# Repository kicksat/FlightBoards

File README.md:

# mainboard
<p align="middle">
Main PCB driving the Kicksat-2 cubesat mothership. Its job is to depoly Sprites, which looks kind  of like this:
  </br>
</br>
Benchtop development hardware looks like this:

</p>

# License

[Creative Commons Attribution-ShareAlike 4.0 International](https://creativecommons.org/licenses/by-sa/4.0/)

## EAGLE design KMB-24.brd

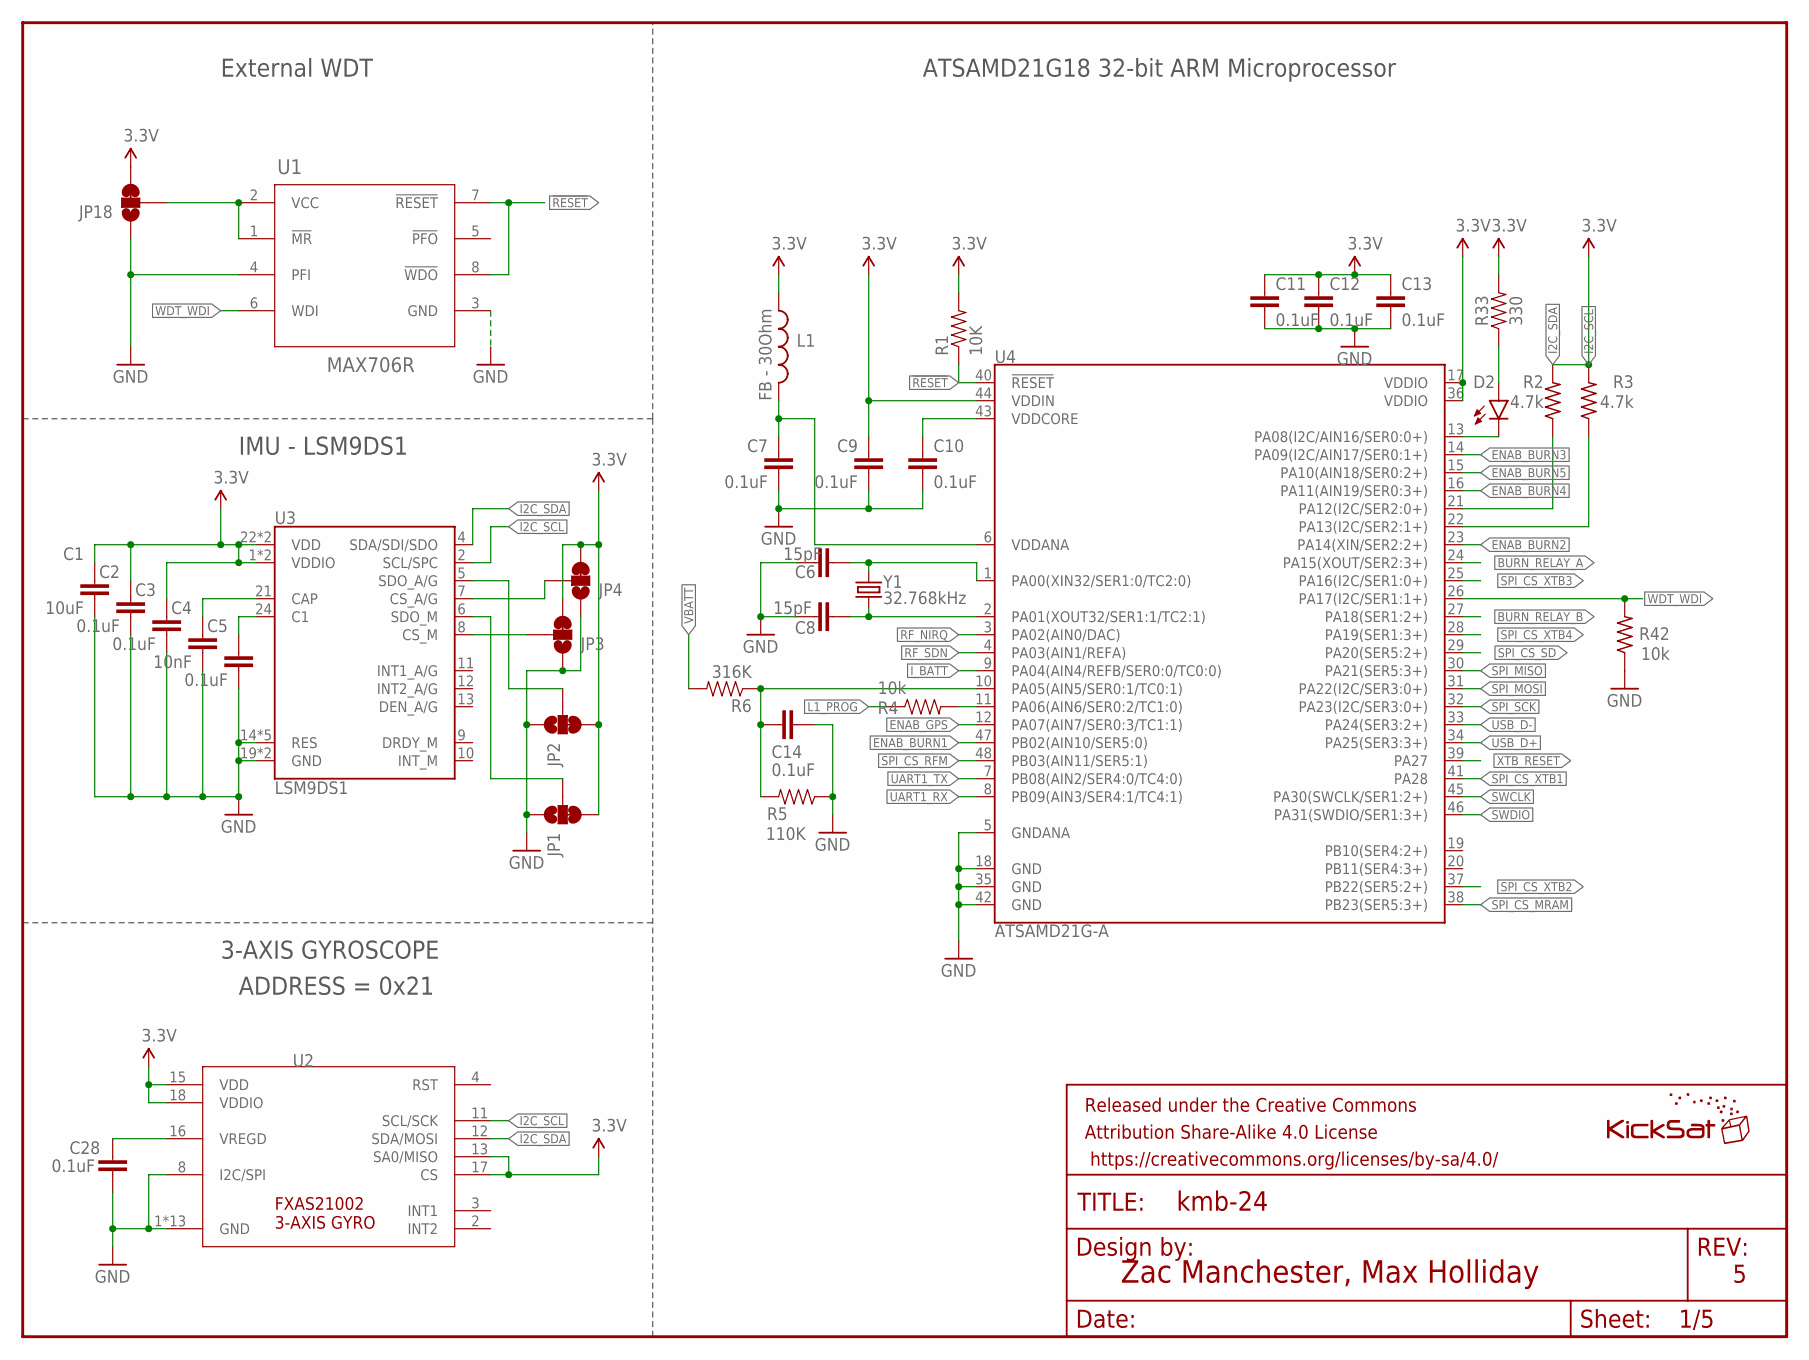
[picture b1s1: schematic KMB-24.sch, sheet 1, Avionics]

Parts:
C1: 10uF; 0603-CAP
C2, C3, C5, C7, C9, C10, C11, C12, C13, C14, C28: 0.1uF; 0603-CAP
C4: 10nF; 0603-CAP
C6, C8: 15pF; 0603-CAP@1
D2: GREEN; LED-0603
FRAME1: FRAME-LETTER; CREATIVE_COMMONS
JP1, JP2, JP3, JP4, JP18: JUMPER-PAD-3-2OF3_NC_BY_TRACE_SMALL; PAD-JUMPER-3-2OF3_NC_BY_TRACE_YES_SILK_FULL_BOX
L1: FB - 30Ohm; 0603
L2: KICKSAT_LOGO
R1: 10K; 0603-RES
R2, R3: 4.7k; R0603
R4: 10k; 0603-RES
R5: 110K; 0603-RES
R6: 316K; 0603-RES
R33: 330; 0603-RES
R42: 10k; R0603
U1: MAX706R; SO8
U2: FXAS21002FXAS21002; QFN50P456X400X100-24
U3: LSM9DS1; LGA24-8X4
U4: ATSAMD21G-A; TQFP-48
Y1: 32.768kHz; CRYSTAL-SMD-3.2X1.5MM

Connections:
3.3V: C1.1, C2.1, C3.1, C9.1, C11.1, C12.1, C13.1, JP1.3, JP2.3, JP3.3, JP4.3, JP18.3, L1.1, R1.2, R2.2, R3.2, R33.2, U2.13 (SA0/MISO), U2.15 (VDD), U2.17 (CS), U2.18 (VDDIO), U3.1 (VDDIO), U3.3 (VDDIO), U3.22 (VDD), U3.23 (VDD), U4.17 (VDDIO), U4.36 (VDDIO), U4.44 (VDDIN); also elsewhere on the board
!RESET: R1.1, U1.7 (!RESET), U1.8 (!WDO), U4.40 (!RESET!); also elsewhere on the board
BURN_RELAY_A: U4.24 (PA15(XOUT/SER2:3+)); also elsewhere on the board
BURN_RELAY_B: U4.27 (PA18(SER1:2+)); also elsewhere on the board
ENAB_BURN1: U4.47 (PB02(AIN10/SER5:0)); also elsewhere on the board
ENAB_BURN2: U4.23 (PA14(XIN/SER2:2+)); also elsewhere on the board
ENAB_BURN3: U4.14 (PA09(I2C/AIN17/SER0:1+)); also elsewhere on the board
ENAB_BURN4: U4.16 (PA11(AIN19/SER0:3+)); also elsewhere on the board
ENAB_BURN5: U4.15 (PA10(AIN18/SER0:2+)); also elsewhere on the board
ENAB_GPS: U4.12 (PA07(AIN7/SER0:3/TC1:1)); also elsewhere on the board
GND: C1.2, C2.2, C3.2, C4.2, C5.2, C6.1, C7.2, C8.2, C9.2, C10.2, C11.2, C12.2, C13.2, C14.2, C28.1, JP1.1, JP2.1, JP3.1, JP4.1, JP18.1, R5.1, R42.1, U1.3 (GND), U1.4 (PFI), U2.1 (GND), U2.5 (GND), U2.6 (GND), U2.7 (GND), U2.8 (I2C/SPI), U2.9 (GND), U2.10 (GND), U2.14 (GND), U2.19 (GND), U2.20 (GND), U2.21 (GND), U2.22 (GND), U2.23 (GND), U2.24 (GND), U3.14 (RES), U3.15 (RES), U3.16 (RES), U3.17 (RES), U3.18 (RES), U3.19 (GND), U3.20 (GND), U4.5 (GNDANA), U4.18 (GND), U4.35 (GND), U4.42 (GND); also elsewhere on the board
I2C_SCL: R3.1, U2.11 (SCL/SCK), U3.2 (SCL/SPC), U4.22 (PA13(I2C/SER2:1+))
I2C_SDA: R2.1, U2.12 (SDA/MOSI), U3.4 (SDA/SDI/SDO), U4.21 (PA12(I2C/SER2:0+))
I2C_SDOA/G: JP2.2, U3.5 (SDO_A/G)
I_BATT: U4.9 (PA04(AIN4/REFB/SER0:0/TC0:0)); also elsewhere on the board
L1_PROG: R4.1; also elsewhere on the board
unnamed: D2.A, R33.1
unnamed: C4.1, U3.21 (CAP)
unnamed: C5.1, U3.24 (C1)
unnamed: JP18.2, U1.1 (!MR), U1.2 (VCC)
unnamed: C14.1, R5.2, R6.1, U4.10 (PA05(AIN5/SER0:1/TC0:1))
unnamed: C7.1, L1.2, U4.6 (VDDANA)
unnamed: JP1.2, U3.6 (SDO_M)
unnamed: C28.2, U2.16 (VREGD)
unnamed: JP3.2, U3.8 (CS_M)
unnamed: JP4.2, U3.7 (CS_A/G)
unnamed: C6.2, U4.1 (PA00(XIN32/SER1:0/TC2:0)), Y1.P$2 (2)
unnamed: C8.1, U4.2 (PA01(XOUT32/SER1:1/TC2:1)), Y1.P$1 (1)
unnamed: R4.2, U4.11 (PA06(AIN6/SER0:2/TC1:0))
unnamed: D2.C, U4.13 (PA08(I2C/AIN16/SER0:0+))
RF_NIRQ: U4.3 (PA02(AIN0/DAC)); also elsewhere on the board
RF_SDN: U4.4 (PA03(AIN1/REFA)); also elsewhere on the board
SPI_CS_MRAM: U4.38 (PB23(SER5:3+)); also elsewhere on the board
SPI_CS_RFM: U4.48 (PB03(AIN11/SER5:1)); also elsewhere on the board
SPI_CS_SD: U4.29 (PA20(SER5:2+)); also elsewhere on the board
SPI_CS_XTB1: U4.41 (PA28); also elsewhere on the board
SPI_CS_XTB2: U4.37 (PB22(SER5:2+)); also elsewhere on the board
SPI_CS_XTB3: U4.25 (PA16(I2C/SER1:0+)); also elsewhere on the board
SPI_CS_XTB4: U4.28 (PA19(SER1:3+)); also elsewhere on the board
SPI_MISO: U4.30 (PA21(SER5:3+)); also elsewhere on the board
SPI_MOSI: U4.31 (PA22(I2C/SER3:0+)); also elsewhere on the board
SPI_SCK: U4.32 (PA23(I2C/SER3:0+)); also elsewhere on the board
SWCLK: U4.45 (PA30(SWCLK/SER1:2+)); also elsewhere on the board
SWDIO: U4.46 (PA31(SWDIO/SER1:3+)); also elsewhere on the board
UART1_RX: U4.8 (PB09(AIN3/SER4:1/TC4:1)); also elsewhere on the board
UART1_TX: U4.7 (PB08(AIN2/SER4:0/TC4:0)); also elsewhere on the board
USB_D+: U4.34 (PA25(SER3:3+)); also elsewhere on the board
USB_D-: U4.33 (PA24(SER3:2+)); also elsewhere on the board
VBATT: R6.2; also elsewhere on the board
VDDCORE3: C10.1, U4.43 (VDDCORE)
WDT_WDI: R42.2, U1.6 (WDI), U4.26 (PA17(I2C/SER1:1+))
XTB_RESET: U4.39 (PA27); also elsewhere on the board

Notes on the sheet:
Zac Manchester, Max Holliday
ATSAMD21G18 32-bit ARM Microprocessor
IMU - LSM9DS1
External WDT
3-AXIS GYROSCOPE
ADDRESS = 0x21

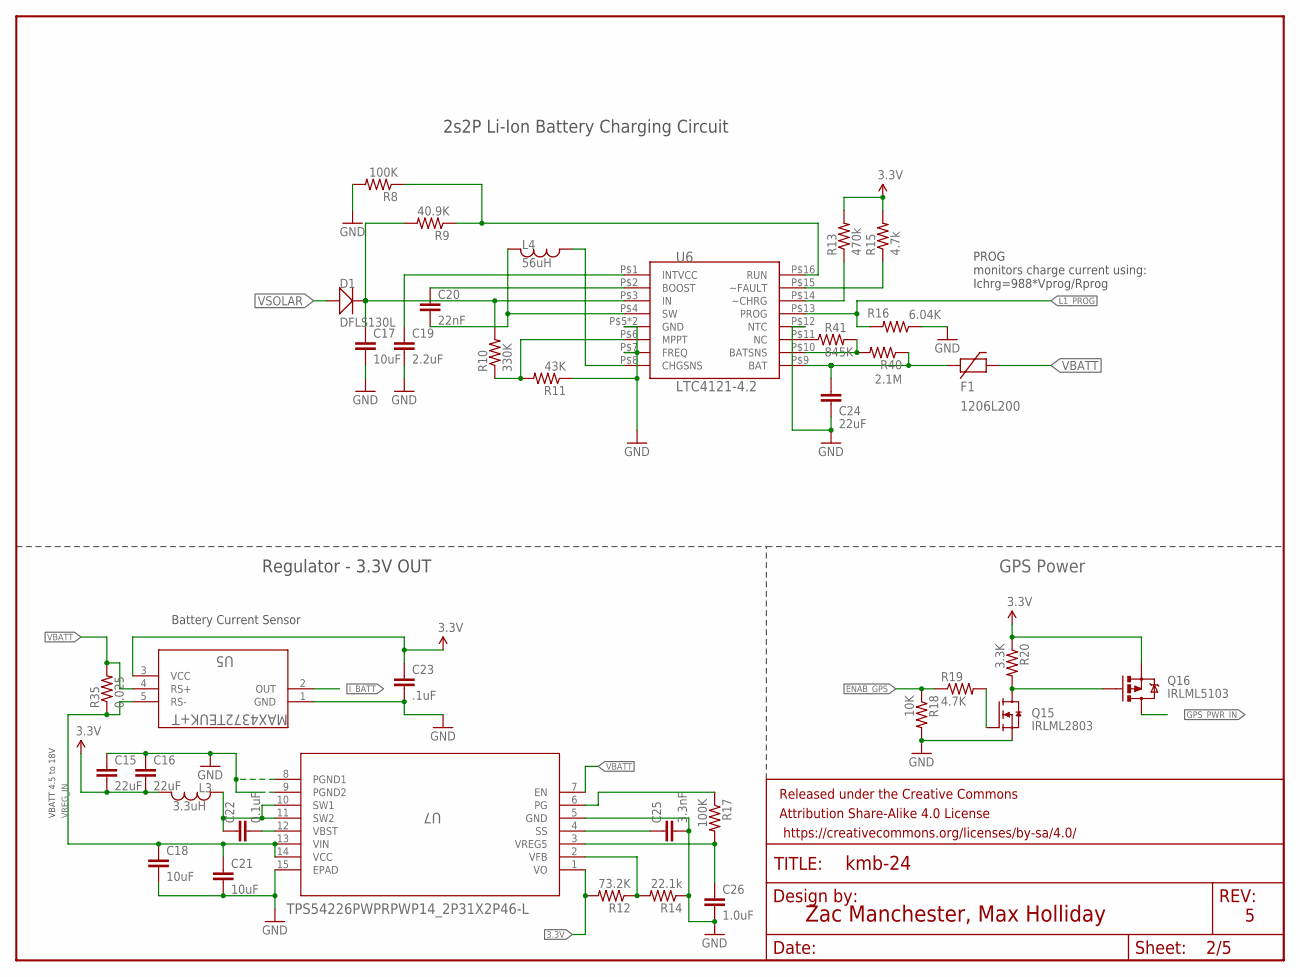
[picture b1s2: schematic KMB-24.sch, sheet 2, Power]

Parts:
C15, C16: 22uF; 0805
C17, C18, C21: 10uF; 0603
C19: 2.2uF; 0603
C20: 22nF; 0603
C22: 0.1uF; 0603
C23: .1uF; 0603-CAP@1
C24: 22uF; 0603
C25: 3.3nF; 0603
C26: 1.0uF; 0603
D1: DFLS130L; PWRDI-123
F1: 1206L200; 1206
FRAME2: FRAME-LETTER; CREATIVE_COMMONS
L3: 3.3uH; 1812
L4: 56uH; 1812
Q15: IRLML2803; SOT-23
Q16: IRLML5103; SOT23-3
R8, R17: 100K; R0603
R9: 40.9K; R0603
R10: 330K; R0603
R11: 43K; R0603
R12: 73.2K; R0603
R13: 470k; R0603
R14: 22.1k; R0603
R15: 4.7k; R0603
R16: 6.04K; R0603
R18: 10K; R0603
R19: 4.7K; R0603
R20: 3.3K; R0603
R35: 0.025; R2512
R40: 2.1M; R0603
R41: 845K; R0603
U5: MAX4372TEUK+T; 21-0057F
U6: LTC4121-4.2; QFN-16-PAD
U7: TPS54226PWPRPWP14_2P31X2P46-L; PWP14_2P31X2P46-L

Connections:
3.3V: C15.2, C16.2, C23.1, L3.P$1, Q16.2 (S), R12.2, R13.2, R15.2, R20.1, U5.3 (VCC), U7.1 (VO); also elsewhere on the board
ENAB_GPS: R18.1, R19.1; also elsewhere on the board
GND: C15.1, C16.1, C17.2, C18.2, C19.2, C21.2, C23.2, C24.2, C25.2, C26.2, Q15.2 (S), R8.2, R11.1, R14.1, R16.1, R18.2, U5.1 (GND), U6.P$5 (GND), U6.P$7 (FREQ), U6.P$12 (NTC), U6.P$17 (GND), U7.5 (GND), U7.8 (PGND1), U7.9 (PGND2), U7.15 (EPAD); also elsewhere on the board
GPS_PWR_IN: Q16.3 (D); also elsewhere on the board
I_BATT: U5.2 (OUT); also elsewhere on the board
L1_CHG: R8.1, R9.1, U6.P$16 (RUN)
L1_FAULTN: R15.1, U6.P$15 (~FAULT)
L1_PROG: R16.2, U6.P$13 (PROG); also elsewhere on the board
LION1: C24.1, F1.1, R40.1, U6.P$9 (BAT)
unnamed: C22.1, L3.P$2, U7.10 (SW1), U7.11 (SW2)
unnamed: Q15.1 (G), R19.2
unnamed: Q15.3 (D), Q16.1 (G), R20.2
unnamed: C22.2, U7.12 (VBST)
unnamed: R40.2, R41.2, U6.P$10 (BATSNS)
unnamed: C20.2, L4.P$1, U6.P$4 (SW)
unnamed: C20.1, U6.P$2 (BOOST)
unnamed: C19.1, U6.P$1 (INTVCC)
unnamed: R10.1, R11.2, U6.P$6 (MPPT)
unnamed: L4.P$2, U6.P$8 (CHGSNS)
unnamed: R13.1, U6.P$14 (~CHRG)
unnamed: C26.1, R17.2, U7.3 (VREG5)
unnamed: C25.1, U7.4 (SS)
unnamed: R12.1, R14.2, U7.2 (VFB)
unnamed: R41.1, U6.P$11 (NC)
PGOOD: R17.1, U7.6 (PG)
VBATT: F1.2, R35.2, U5.4 (RS+), U7.7 (EN); also elsewhere on the board
VREG_IN: C18.1, C21.1, R35.1, U5.5 (RS-), U7.13 (VIN), U7.14 (VCC)
VSOLAR: D1.A; also elsewhere on the board
VSOLAR_IN: C17.1, D1.C, R9.2, R10.2, U6.P$3 (IN)

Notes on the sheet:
Battery Current Sensor
Zac Manchester, Max Holliday
GPS Power
2s2P Li-Ion Battery Charging Circuit
Regulator - 3.3V OUT
VBATT 4.5 to 18V
PROG monitors charge current using: Ichrg=988*Vprog/Rprog

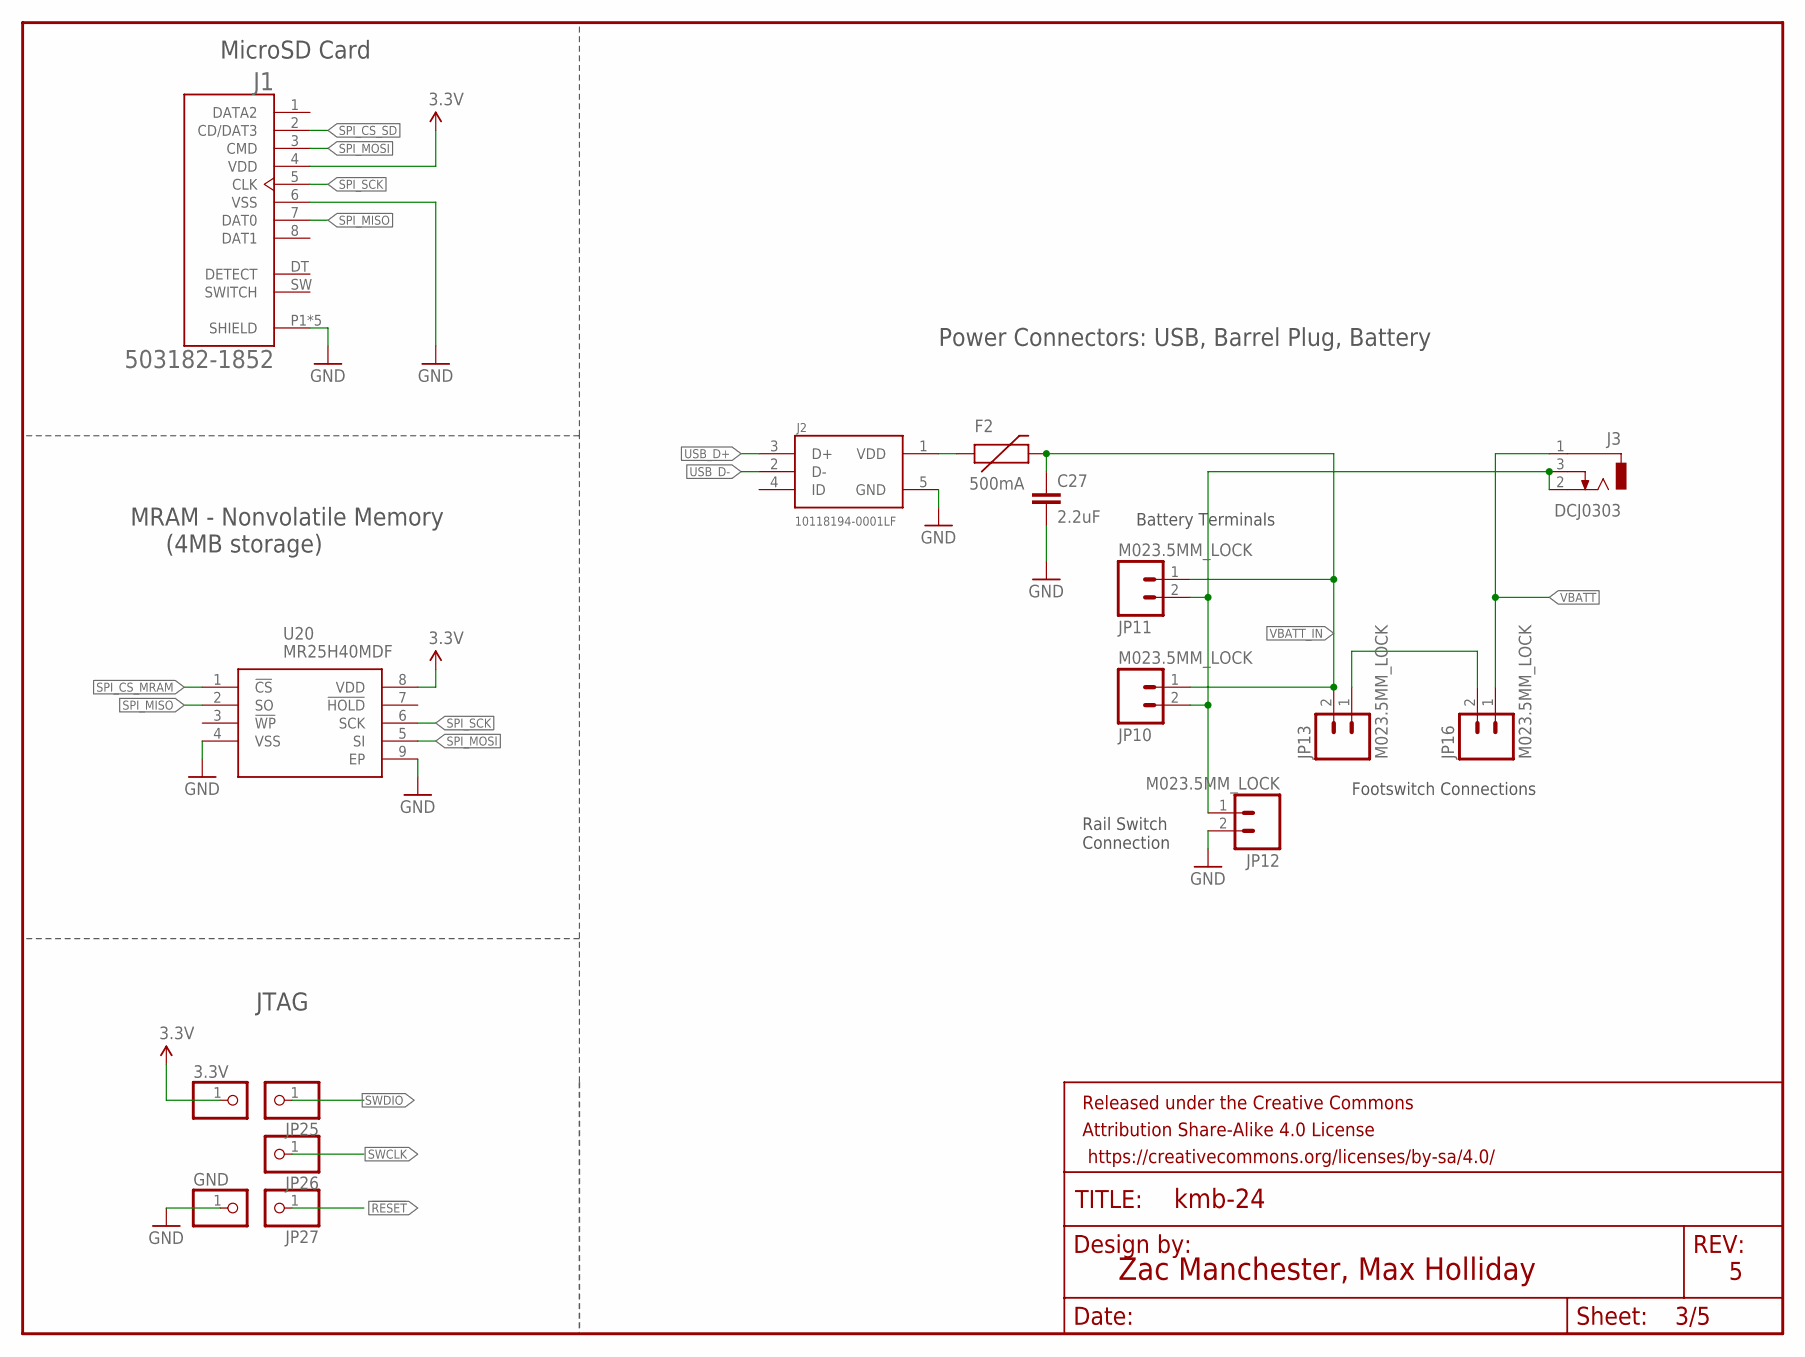
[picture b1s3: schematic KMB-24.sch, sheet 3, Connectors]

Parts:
3.3V: PINHD-1X1; 1X01
C27: 2.2uF; 0603
F2: 500mA; PTC-1206
FRAME3: FRAME-LETTER; CREATIVE_COMMONS
GND: PINHD-1X1; 1X01
J1: 503182-1852; MOLEX_503182-1852
J2: 10118194-0001LF; FRAMATOME_10118194-0001LF
J3: DCJ0303
JP10, JP11, JP12, JP13, JP16: M023.5MM_LOCK; SCREWTERMINAL-3.5MM-2_LOCK
JP25, JP26, JP27: PINHD-1X1; 1X01
U20: MR25H40MDF; SON127P600X500X90-9N

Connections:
3.3V: 3.3V.1, J1.4 (VDD), U20.8 (VDD); also elsewhere on the board
!RESET: JP27.1; also elsewhere on the board
GND: C27.2, GND.1, J1.6 (VSS), J1.P1 (SHIELD), J1.P2 (SHIELD), J1.P3 (SHIELD), J1.P4 (SHIELD), J1.P5 (SHIELD), J2.5 (GND), JP12.2, U20.4 (VSS), U20.9 (EP); also elsewhere on the board
unnamed: JP13.1, JP16.2
unnamed: F2.1, J2.1 (VDD)
unnamed: J3.2, J3.3, JP10.2, JP11.2, JP12.1
SPI_CS_MRAM: U20.1 (!CS); also elsewhere on the board
SPI_CS_SD: J1.2 (CD/DAT3); also elsewhere on the board
SPI_MISO: J1.7 (DAT0), U20.2 (SO); also elsewhere on the board
SPI_MOSI: J1.3 (CMD), U20.5 (SI); also elsewhere on the board
SPI_SCK: J1.5 (CLK), U20.6 (SCK); also elsewhere on the board
SWCLK: JP26.1; also elsewhere on the board
SWDIO: JP25.1; also elsewhere on the board
USB_D+: J2.3 (D+); also elsewhere on the board
USB_D-: J2.2 (D-); also elsewhere on the board
VBATT: J3.1, JP16.1; also elsewhere on the board
VBATT_IN: C27.1, F2.2, JP10.1, JP11.1, JP13.2

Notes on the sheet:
Footswitch Connections
Battery Terminals
Rail Switch Connection
Zac Manchester, Max Holliday
JTAG
Power Connectors: USB, Barrel Plug, Battery
MicroSD Card
MRAM - Nonvolatile Memory (4MB storage)

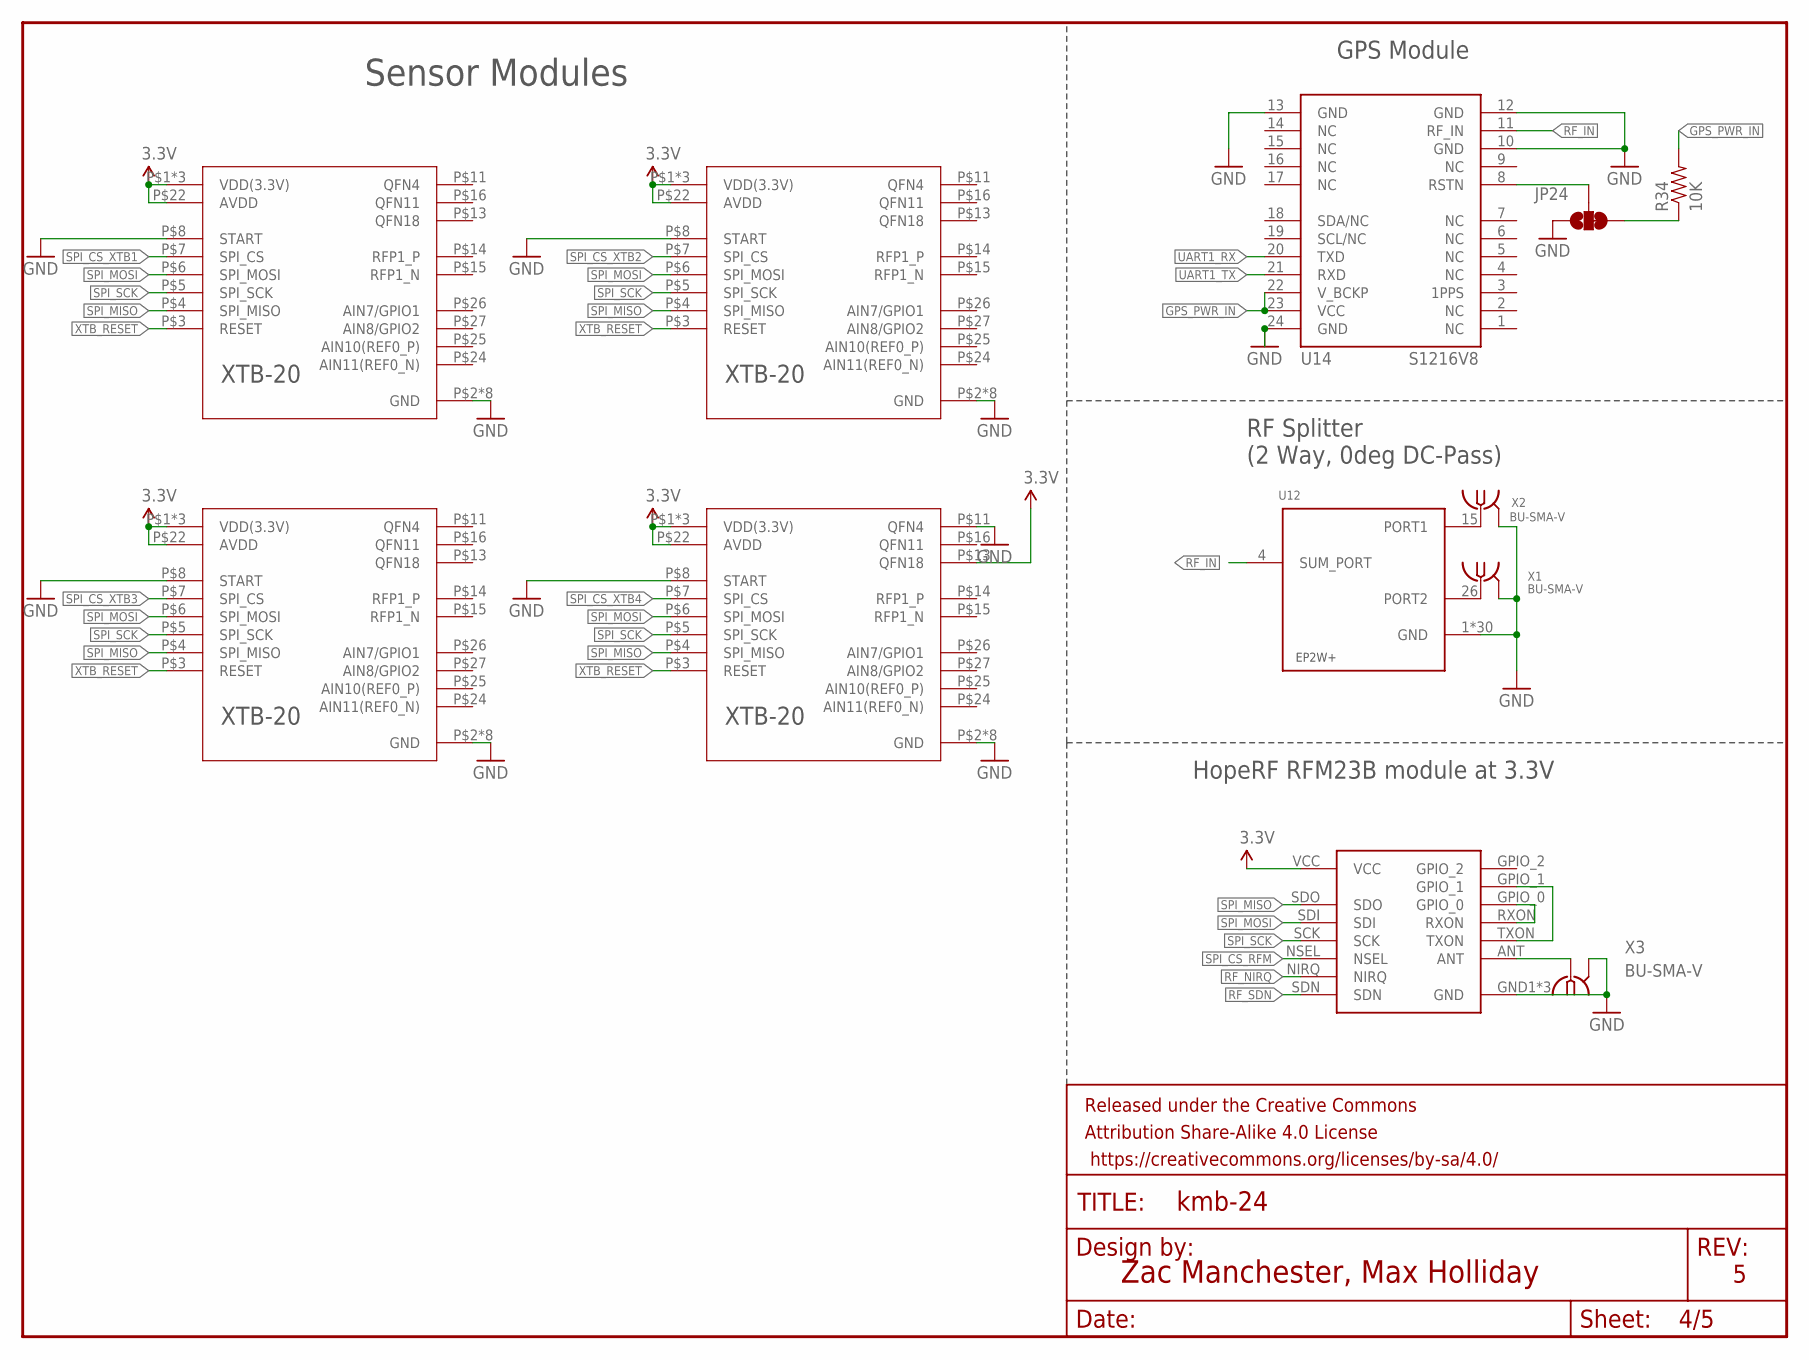
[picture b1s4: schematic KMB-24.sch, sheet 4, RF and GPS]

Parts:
FRAME4: FRAME-LETTER; CREATIVE_COMMONS
JP24: JUMPER-PAD-3-2OF3_NC_BY_TRACE_SMALL; PAD-JUMPER-3-2OF3_NC_BY_TRACE_YES_SILK_FULL_BOX
R34: 10K; 0603-RES
U12: EP2W+; QFN32-5X5MM
U13: RFM23BP
U14: S1216V8; S1216_24PIN_PACKAGE
U15, U16, U17, U18: XTB_2018_07_15; XTB28_MEZ
X1, X2, X3: BU-SMA-V

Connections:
3.3V: U13.VCC, U15.P$1 (VDD(3.3V)), U15.P$20 (VDD(3.3V)), U15.P$22 (AVDD), U15.P$28 (VDD(3.3V)), U16.P$1 (VDD(3.3V)), U16.P$20 (VDD(3.3V)), U16.P$22 (AVDD), U16.P$28 (VDD(3.3V)), U17.P$1 (VDD(3.3V)), U17.P$20 (VDD(3.3V)), U17.P$22 (AVDD), U17.P$28 (VDD(3.3V)), U18.P$1 (VDD(3.3V)), U18.P$13 (QFN18), U18.P$20 (VDD(3.3V)), U18.P$22 (AVDD), U18.P$28 (VDD(3.3V)); also elsewhere on the board
GND: JP24.1, U12.1 (GND), U12.2 (GND), U12.3 (GND), U12.5 (GND), U12.6 (GND), U12.7 (GND), U12.8 (GND), U12.9 (GND), U12.10 (GND), U12.11 (GND), U12.12 (GND), U12.13 (GND), U12.14 (GND), U12.16 (GND), U12.17 (GND), U12.18 (GND), U12.19 (GND), U12.20 (GND), U12.21 (GND), U12.22 (GND), U12.23 (GND), U12.24 (GND), U12.25 (GND), U12.27 (GND), U12.28 (GND), U12.29 (GND), U12.30 (GND), U12.31 (GND), U12.32 (GND), U12.EP (GND), U13.GND1 (GND), U13.GND2 (GND), U13.GND3 (GND), U14.10 (GND), U14.12 (GND), U14.13 (GND), U14.24 (GND), U15.P$2 (GND), U15.P$8 (START), U15.P$9 (GND), U15.P$10 (GND), U15.P$12 (GND), U15.P$17 (GND), U15.P$19 (GND), U15.P$21 (GND), U15.P$23 (GND), U16.P$2 (GND), U16.P$8 (START), U16.P$9 (GND), U16.P$10 (GND), U16.P$12 (GND), U16.P$17 (GND), U16.P$19 (GND), U16.P$21 (GND), U16.P$23 (GND), U17.P$2 (GND), U17.P$8 (START), U17.P$9 (GND), U17.P$10 (GND), U17.P$12 (GND), U17.P$17 (GND), U17.P$19 (GND), U17.P$21 (GND), U17.P$23 (GND), U18.P$2 (GND), U18.P$8 (START), U18.P$9 (GND), U18.P$10 (GND), U18.P$11 (QFN4), U18.P$12 (GND), U18.P$17 (GND), U18.P$19 (GND), U18.P$21 (GND), U18.P$23 (GND), X1.2, X1.3 (2), X1.4 (2), X1.5 (2), X2.2, X2.3 (2), X2.4 (2), X2.5 (2), X3.2, X3.3 (2), X3.4 (2), X3.5 (2); also elsewhere on the board
GPS_PWR_IN: R34.2, U14.22 (V_BCKP), U14.23 (VCC); also elsewhere on the board
unnamed: JP24.2, U14.8 (RSTN)
unnamed: U12.15 (PORT1), X2.1
unnamed: U12.26 (PORT2), X1.1
unnamed: U13.ANT, X3.1
unnamed: JP24.3, R34.1
unnamed: U13.GPIO_0, U13.RXON
unnamed: U13.GPIO_1, U13.TXON
RF_IN: U12.4 (SUM_PORT), U14.11 (RF_IN)
RF_NIRQ: U13.NIRQ; also elsewhere on the board
RF_SDN: U13.SDN; also elsewhere on the board
SPI_CS_RFM: U13.NSEL; also elsewhere on the board
SPI_CS_XTB1: U15.P$7 (SPI_CS); also elsewhere on the board
SPI_CS_XTB2: U16.P$7 (SPI_CS); also elsewhere on the board
SPI_CS_XTB3: U17.P$7 (SPI_CS); also elsewhere on the board
SPI_CS_XTB4: U18.P$7 (SPI_CS); also elsewhere on the board
SPI_MISO: U13.SDO, U15.P$4 (SPI_MISO), U16.P$4 (SPI_MISO), U17.P$4 (SPI_MISO), U18.P$4 (SPI_MISO); also elsewhere on the board
SPI_MOSI: U13.SDI, U15.P$6 (SPI_MOSI), U16.P$6 (SPI_MOSI), U17.P$6 (SPI_MOSI), U18.P$6 (SPI_MOSI); also elsewhere on the board
SPI_SCK: U13.SCK, U15.P$5 (SPI_SCK), U16.P$5 (SPI_SCK), U17.P$5 (SPI_SCK), U18.P$5 (SPI_SCK); also elsewhere on the board
UART1_RX: U14.20 (TXD); also elsewhere on the board
UART1_TX: U14.21 (RXD); also elsewhere on the board
XTB_RESET: U15.P$3 (RESET), U16.P$3 (RESET), U17.P$3 (RESET), U18.P$3 (RESET); also elsewhere on the board

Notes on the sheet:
GPS Module
Zac Manchester, Max Holliday
HopeRF RFM23B module at 3.3V
RF Splitter (2 Way, 0deg DC-Pass)
Sensor Modules

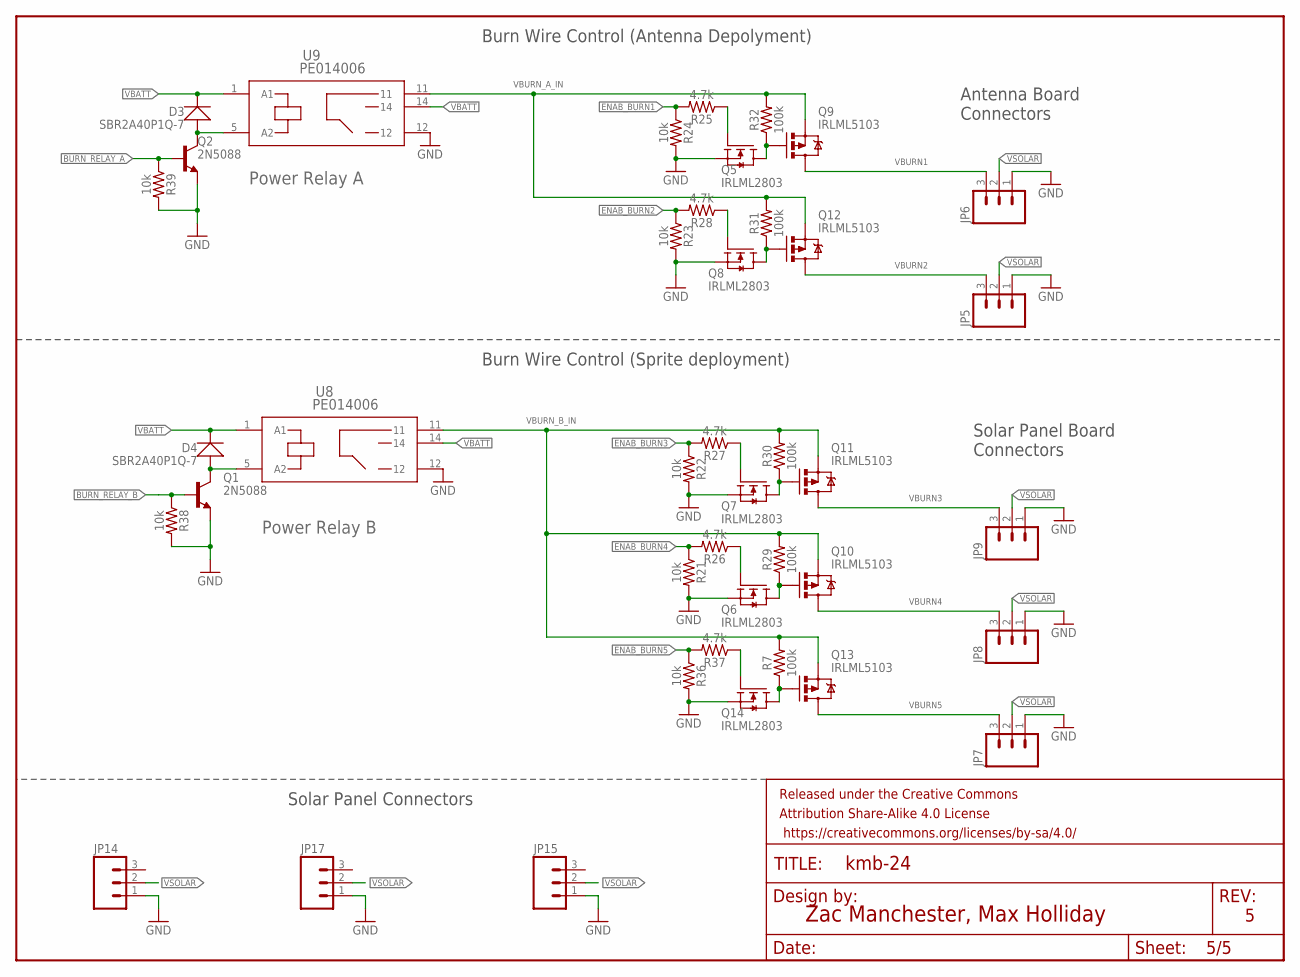
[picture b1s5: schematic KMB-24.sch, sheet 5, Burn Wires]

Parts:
D3, D4: SBR2A40P1Q-7; PWRDI-123
FRAME5: FRAME-LETTER; CREATIVE_COMMONS
JP5, JP6, JP7, JP8, JP9, JP14, JP15, JP17: M03POLAR_LOCK; MOLEX-1X3_LOCK
Q1, Q2: 2N5088; SOT23
Q5, Q6, Q7, Q8, Q14: IRLML2803; SOT-23
Q9, Q10, Q11, Q12, Q13: IRLML5103; SOT23-3
R7, R29, R30, R31, R32: 100k; 0603
R21, R22, R23, R24, R36, R38, R39: 10k; 0603
R25, R26, R27, R28, R37: 4.7k; 0603
U8, U9: PE014006; RELAY5-PE_CO

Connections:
BURN_RELAY_A: Q2.1 (B), R39.1; also elsewhere on the board
BURN_RELAY_B: Q1.1 (B), R38.1; also elsewhere on the board
ENAB_BURN1: R24.1, R25.2; also elsewhere on the board
ENAB_BURN2: R23.1, R28.2; also elsewhere on the board
ENAB_BURN3: R22.1, R27.2; also elsewhere on the board
ENAB_BURN4: R21.1, R26.2; also elsewhere on the board
ENAB_BURN5: R36.1, R37.2; also elsewhere on the board
GND: JP5.1, JP6.1, JP7.1, JP8.1, JP9.1, JP14.1, JP15.1, JP17.1, Q1.2 (E), Q2.2 (E), Q5.2 (S), Q6.2 (S), Q7.2 (S), Q8.2 (S), Q14.2 (S), R21.2, R22.2, R23.2, R24.2, R36.2, R38.2, R39.2, U8.12, U9.12; also elsewhere on the board
unnamed: Q6.1 (G), R26.1
unnamed: Q5.3 (D), Q9.1 (G), R32.1
unnamed: Q5.1 (G), R25.1
unnamed: Q8.3 (D), Q12.1 (G), R31.1
unnamed: Q8.1 (G), R28.1
unnamed: Q7.1 (G), R27.1
unnamed: D3.A, Q2.3 (C), U9.5 (A2)
unnamed: Q7.3 (D), Q11.1 (G), R30.1
unnamed: Q6.3 (D), Q10.1 (G), R29.1
unnamed: Q13.1 (G), Q14.3 (D), R7.1
unnamed: Q14.1 (G), R37.1
unnamed: D4.A, Q1.3 (C), U8.5 (A2)
VBATT: D3.C, D4.C, U8.1 (A1), U8.14, U9.1 (A1), U9.14; also elsewhere on the board
VBURN1: JP6.3, Q9.3 (D)
VBURN2: JP5.3, Q12.3 (D)
VBURN3: JP9.3, Q11.3 (D)
VBURN4: JP8.3, Q10.3 (D)
VBURN5: JP7.3, Q13.3 (D)
VBURN_A_IN: Q9.2 (S), Q12.2 (S), R31.2, R32.2, U9.11
VBURN_B_IN: Q10.2 (S), Q11.2 (S), Q13.2 (S), R7.2, R29.2, R30.2, U8.11
VSOLAR: JP5.2, JP6.2, JP7.2, JP8.2, JP9.2, JP14.2, JP15.2, JP17.2; also elsewhere on the board

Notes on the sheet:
Zac Manchester, Max Holliday
Power Relay A
Burn Wire Control (Antenna Depolyment)
Burn Wire Control (Sprite deployment)
Power Relay B
Antenna Board Connectors
Solar Panel Board Connectors
Solar Panel Connectors

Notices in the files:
parts and their libraries:
SparkFun-Capacitors: Licensing: Creative Commons ShareAlike 4.0 International - https://creativecommons.org/licenses/by-sa/4.0
SparkFun-Aesthetics: Released under the Creative Commons Attribution Share-Alike 4.0 License
SparkFun-Aesthetics: Released under the Creative Commons
